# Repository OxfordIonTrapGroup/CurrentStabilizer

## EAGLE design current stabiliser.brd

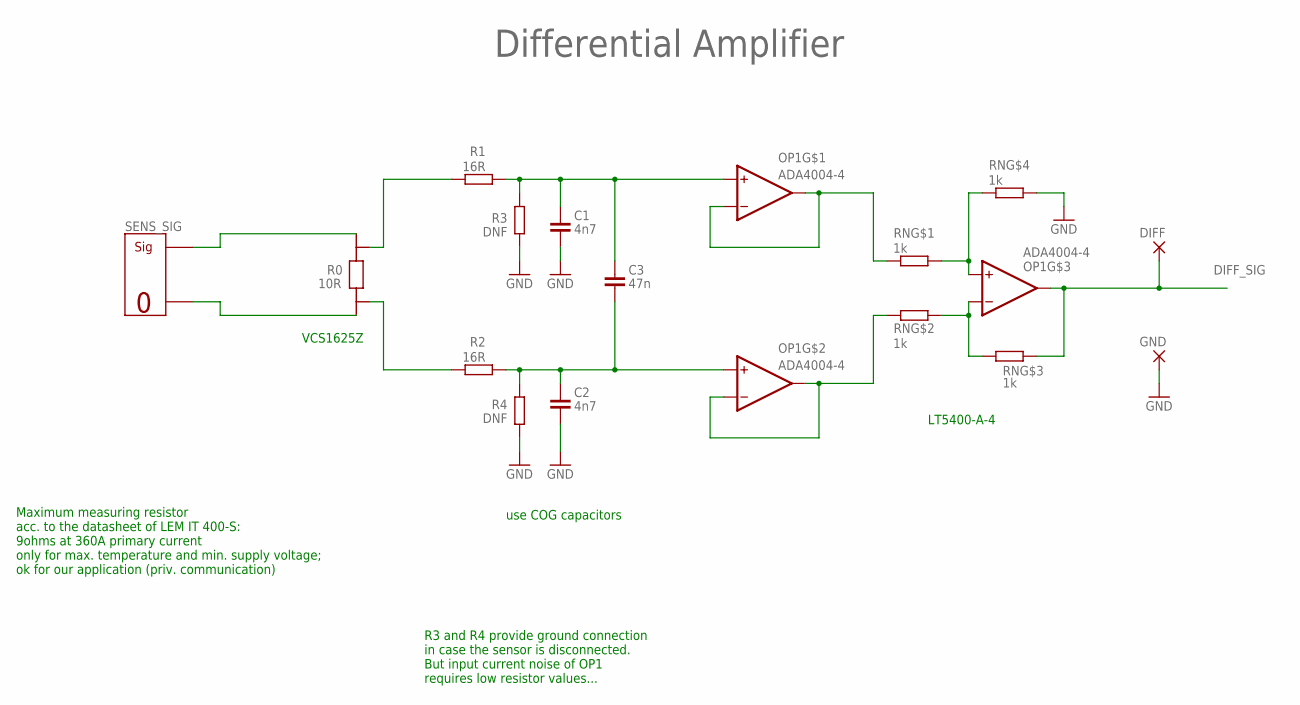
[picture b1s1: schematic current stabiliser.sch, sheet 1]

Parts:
C1, C2: 4n7; 0603
C3: 47n; 0603
DIFF: TESTPOINT
GND: TESTPOINT
OP1: ADA4004-4; SO14
R0: 10R; VCS1625Z
R1, R2: 16R; 0603
R3, R4: DNF; 0603
RN: 1k; MSOP8-EP
SENS_SIG: MOLEX_SIG_2PIN; MOLEX-2PIN

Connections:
DIFF_SIG: DIFF.P$1, OP1.P$8 (OUT), RN.3 (1); also elsewhere on the board
GND: C1.2, C2.2, GND.P$1, R3.1, R4.1, RN.5 (2); also elsewhere on the board
unnamed: R0.P$1 (I1), SENS_SIG.2 (SIG)
unnamed: C2.1, C3.2, OP1.P$5 (+IN), R2.2, R4.2
unnamed: R0.P$4 (E2), R2.1
unnamed: R0.P$3 (E1), R1.1
unnamed: C1.1, C3.1, OP1.P$3 (+IN), R1.2, R3.2
unnamed: OP1.P$1 (OUT), OP1.P$2 (-IN), RN.1
unnamed: OP1.P$6 (-IN), OP1.P$7 (OUT), RN.2 (1)
unnamed: OP1.P$10 (+IN), RN.4 (1), RN.8 (2)
unnamed: OP1.P$9 (-IN), RN.6 (2), RN.7 (2)
SENS_RETURN: R0.P$2 (I2), SENS_SIG.1 (GND)

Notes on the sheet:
Differential Amplifier
use COG capacitors
R3 and R4 provide ground connection in case the sensor is disconnected. But input current noise of OP1 requires low resistor values...
Maximum measuring resistor acc. to the datasheet of LEM IT 400-S: 9ohms at 360A primary current only for max. temperature and min. supply voltage; ok for our application (priv. communication)
VCS1625Z
LT5400-A-4

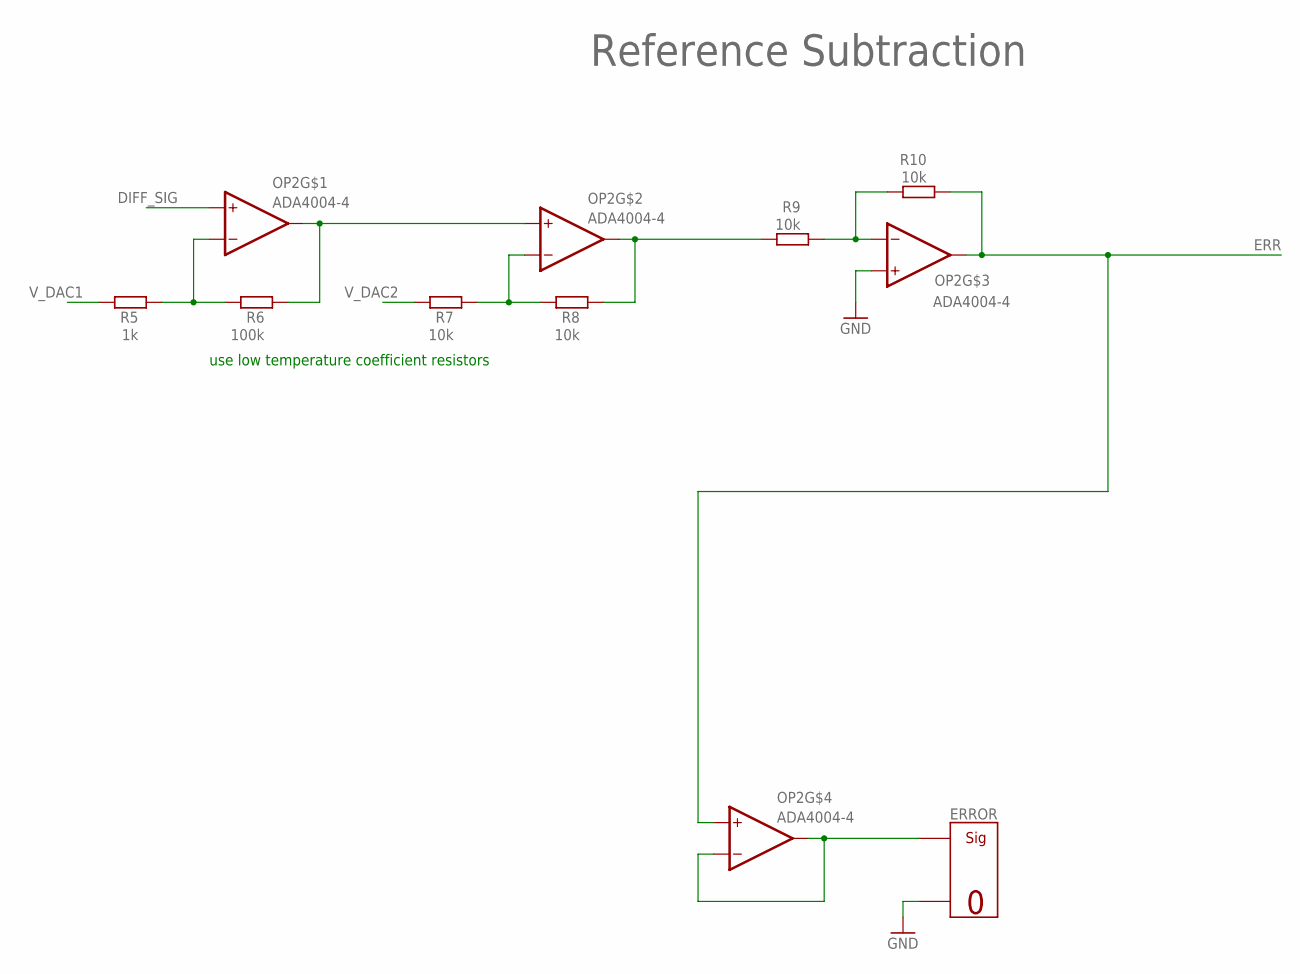
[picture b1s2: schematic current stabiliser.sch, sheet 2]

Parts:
ERROR: MOLEX_SIG_2PIN; MOLEX-2PIN
OP2: ADA4004-4; SO14
R5: 1k; 0603
R6: 100k; 0603
R7, R8, R9, R10: 10k; 0603

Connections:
DIFF_SIG: OP2.P$3 (+IN); also elsewhere on the board
ERR: OP2.P$8 (OUT), OP2.P$12 (+IN), R10.2; also elsewhere on the board
GND: ERROR.1 (GND), OP2.P$10 (+IN); also elsewhere on the board
unnamed: OP2.P$2 (-IN), R5.2, R6.1
unnamed: OP2.P$9 (-IN), R9.2, R10.1
unnamed: OP2.P$1 (OUT), OP2.P$5 (+IN), R6.2
unnamed: OP2.P$6 (-IN), R7.2, R8.1
unnamed: OP2.P$7 (OUT), R8.2, R9.1
unnamed: ERROR.2 (SIG), OP2.P$13 (-IN), OP2.P$14 (OUT)
V_DAC1: R5.1; also elsewhere on the board
V_DAC2: R7.1; also elsewhere on the board

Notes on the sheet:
Reference Subtraction
use low temperature coefficient resistors

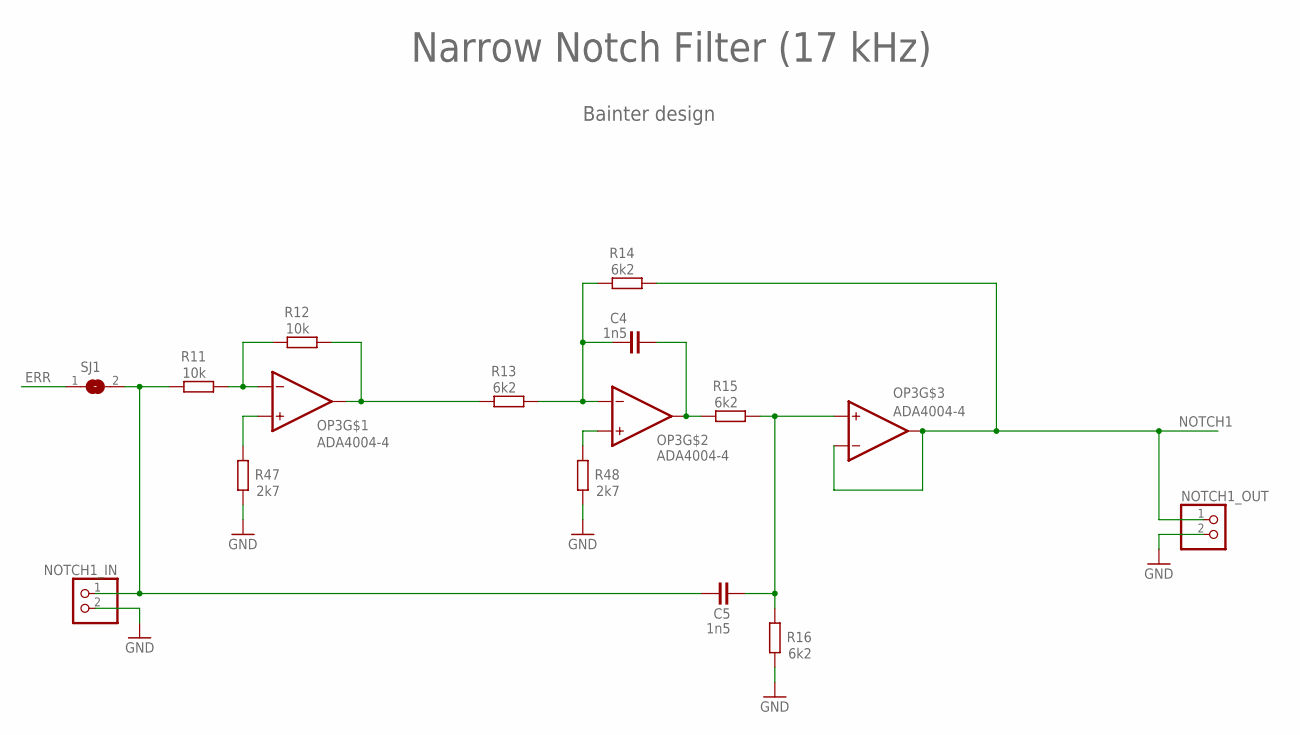
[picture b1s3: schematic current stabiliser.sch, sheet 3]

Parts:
C4, C5: 1n5; 0603
NOTCH1_IN, NOTCH1_OUT: PINHD-1X2; 1X02
OP3: ADA4004-4; SO14
R11, R12: 10k; 0603
R13, R14, R15, R16: 6k2; 0603
R47, R48: 2k7; 0603
SJ1: SJ

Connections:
ERR: SJ1.1; also elsewhere on the board
GND: NOTCH1_IN.2, NOTCH1_OUT.2, R16.2, R47.2, R48.2; also elsewhere on the board
unnamed: OP3.P$2 (-IN), R11.2, R12.1
unnamed: OP3.P$1 (OUT), R12.2, R13.1
unnamed: C4.1, OP3.P$6 (-IN), R13.2, R14.1
unnamed: C4.2, OP3.P$7 (OUT), R15.1
unnamed: C5.2, OP3.P$10 (+IN), R15.2, R16.1
unnamed: C5.1, NOTCH1_IN.1, R11.1, SJ1.2
unnamed: OP3.P$3 (+IN), R47.1
unnamed: OP3.P$5 (+IN), R48.1
NOTCH1: NOTCH1_OUT.1, OP3.P$8 (OUT), OP3.P$9 (-IN), R14.2; also elsewhere on the board

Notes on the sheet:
Narrow Notch Filter (17 kHz)
Bainter design

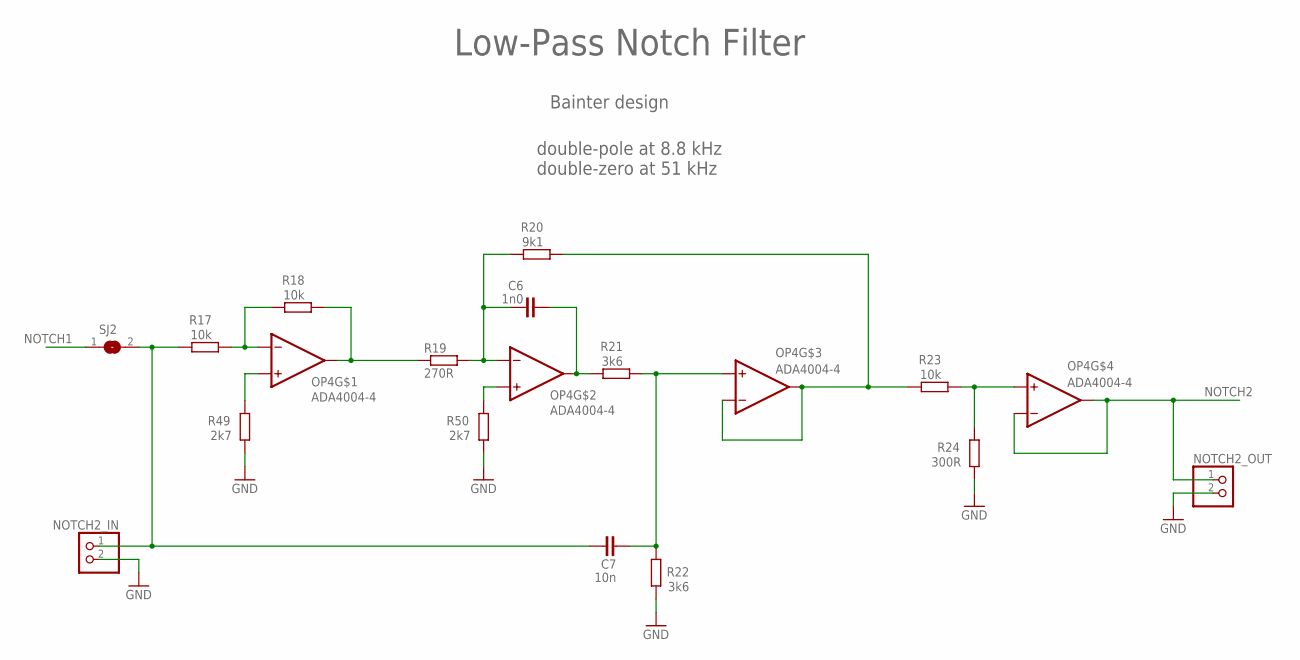
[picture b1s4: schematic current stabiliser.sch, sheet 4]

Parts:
C6: 1n0; 0603
C7: 10n; 0603
NOTCH2_IN, NOTCH2_OUT: PINHD-1X2; 1X02
OP4: ADA4004-4; SO14
R17, R18, R23: 10k; 0603
R19: 270R; 0603
R20: 9k1; 0603
R21, R22: 3k6; 0603
R24: 300R; 0603
R49, R50: 2k7; 0603
SJ2: SJ

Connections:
GND: NOTCH2_IN.2, NOTCH2_OUT.2, R22.1, R24.1, R49.1, R50.1; also elsewhere on the board
unnamed: OP4.P$2 (-IN), R17.2, R18.1
unnamed: OP4.P$1 (OUT), R18.2, R19.1
unnamed: C6.1, OP4.P$6 (-IN), R19.2, R20.1
unnamed: C7.2, OP4.P$10 (+IN), R21.2, R22.2
unnamed: C6.2, OP4.P$7 (OUT), R21.1
unnamed: OP4.P$8 (OUT), OP4.P$9 (-IN), R20.2, R23.1
unnamed: OP4.P$12 (+IN), R23.2, R24.2
unnamed: C7.1, NOTCH2_IN.1, R17.1, SJ2.2
unnamed: OP4.P$3 (+IN), R49.2
unnamed: OP4.P$5 (+IN), R50.2
NOTCH1: SJ2.1; also elsewhere on the board
NOTCH2: NOTCH2_OUT.1, OP4.P$13 (-IN), OP4.P$14 (OUT); also elsewhere on the board

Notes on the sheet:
Low-Pass Notch Filter
double-pole at 8.8 kHz double-zero at 51 kHz
Bainter design

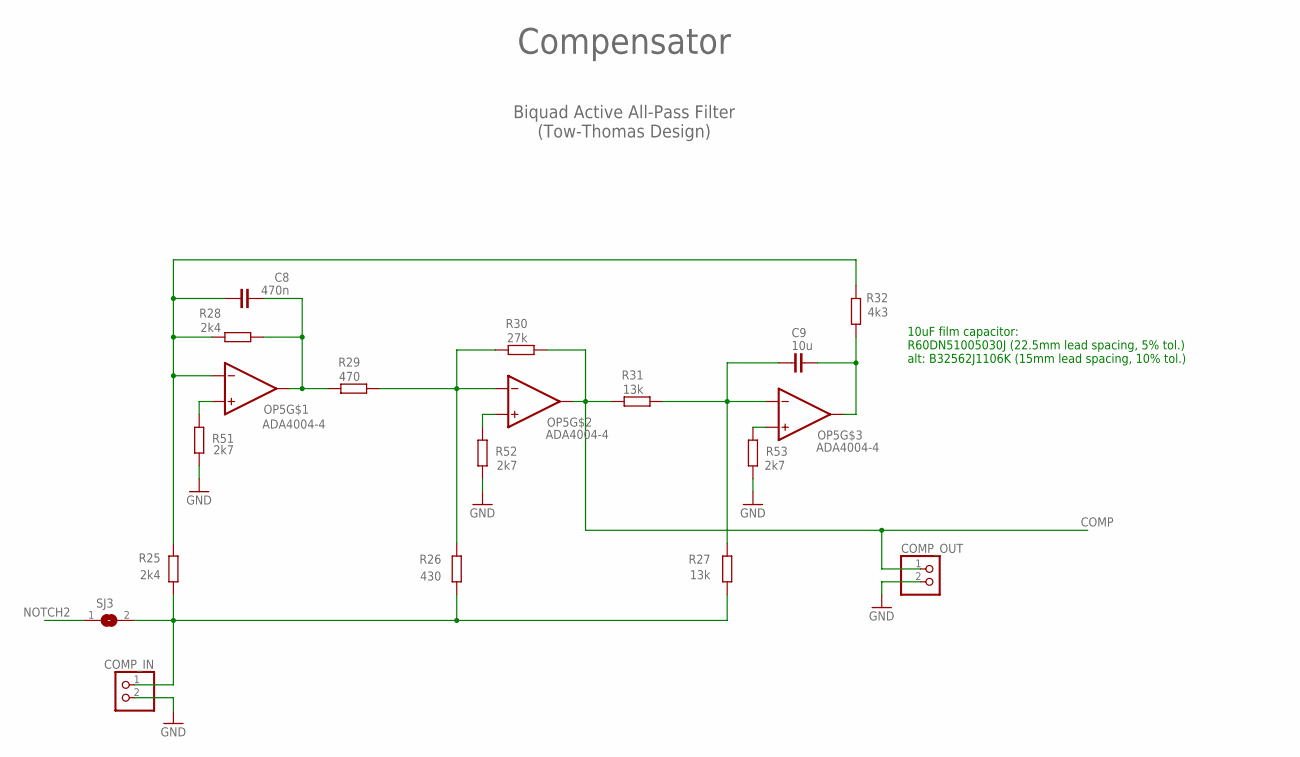
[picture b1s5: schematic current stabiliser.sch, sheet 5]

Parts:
C8: 470n; 0603
C9: 10u; CAP-26.5X8.5
COMP_IN: PINHD-1X2; 1X02
COMP_OUT: PINHD-1X2; 1X02
OP5: ADA4004-4; SO14
R25, R28: 2k4; 0603
R26: 430; 0603
R27, R31: 13k; 0603
R29: 470; 0603
R30: 27k; 0603
R32: 4k3; 0603
R51, R52, R53: 2k7; 0603
SJ3: SJ

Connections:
COMP: COMP_OUT.1, OP5.P$7 (OUT), R30.2, R31.1; also elsewhere on the board
GND: COMP_IN.2, COMP_OUT.2, R51.1, R52.1, R53.1; also elsewhere on the board
unnamed: C8.1, OP5.P$2 (-IN), R25.2, R28.1, R32.2
unnamed: OP5.P$6 (-IN), R26.2, R29.2, R30.1
unnamed: C9.P$1 (1), OP5.P$9 (-IN), R27.2, R31.2
unnamed: C8.2, OP5.P$1 (OUT), R28.2, R29.1
unnamed: C9.P$2 (2), OP5.P$8 (OUT), R32.1
unnamed: COMP_IN.1, R25.1, R26.1, R27.1, SJ3.2
unnamed: OP5.P$3 (+IN), R51.2
unnamed: OP5.P$5 (+IN), R52.2
unnamed: OP5.P$10 (+IN), R53.2
NOTCH2: SJ3.1; also elsewhere on the board

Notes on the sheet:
10uF film capacitor: R60DN51005030J (22.5mm lead spacing, 5% tol.) alt: B32562J1106K (15mm lead spacing, 10% tol.)
Compensator
Biquad Active All-Pass Filter (Tow-Thomas Design)

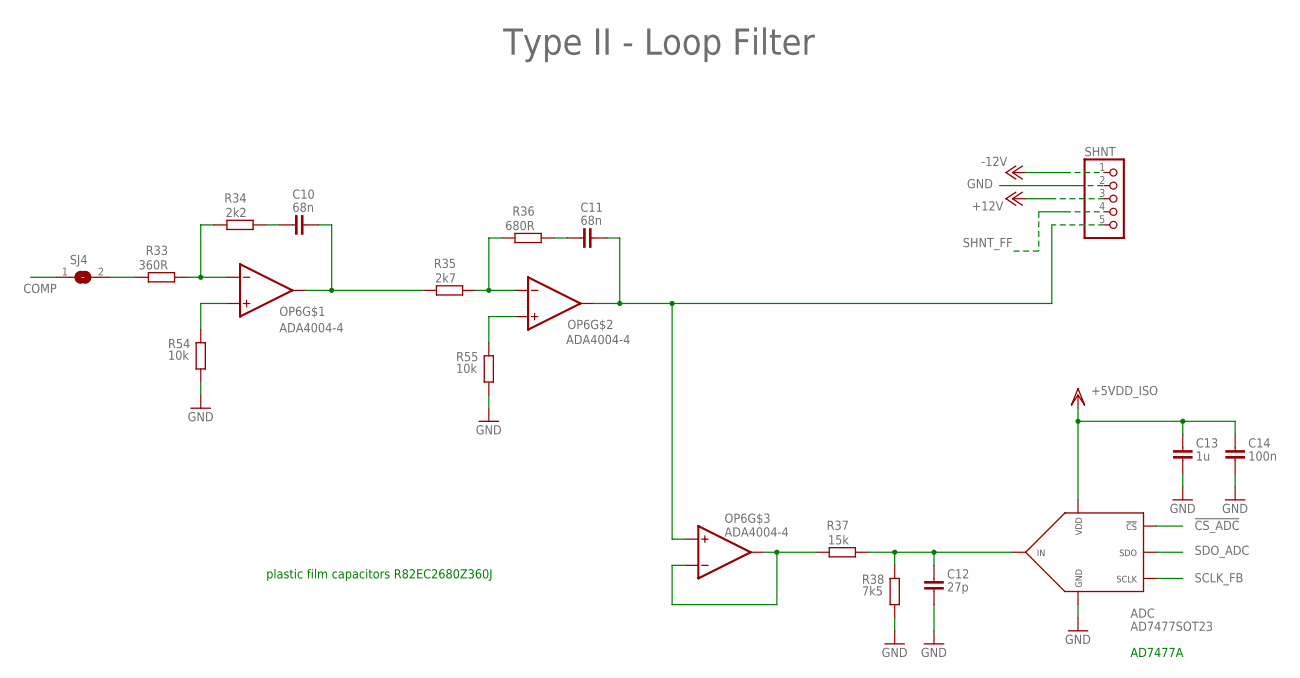
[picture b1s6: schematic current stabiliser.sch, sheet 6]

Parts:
ADC: AD7477SOT23; SOT23-6
C10, C11: 68n; CAP-R82EC-7.2X2.5
C12: 27p; 0603
C13: 1u; 0805
C14: 100n; 0603
OP6: ADA4004-4; SO14
R33: 360R; 0603
R34: 2k2; 0603
R35: 2k7; 0603
R36: 680R; 0603
R37: 15k; 0603
R38: 7k5; 0603
R54, R55: 10k; 0603
SHNT: MOLEX-KK-1X5; MOLEX-KK-5PIN
SJ4: SJ

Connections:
!CS_ADC: ADC.6 (!CS); also elsewhere on the board
+5VDD_ISO: ADC.1 (VDD), C13.1, C14.1; also elsewhere on the board
+12V: SHNT.3; also elsewhere on the board
-12V: SHNT.1; also elsewhere on the board
COMP: SJ4.1; also elsewhere on the board
GND: ADC.2 (GND), C12.2, C13.2, C14.2, R38.1, R54.1, R55.1, SHNT.2; also elsewhere on the board
unnamed: OP6.P$2 (-IN), R33.2, R34.1
unnamed: OP6.P$3 (+IN), R54.2
unnamed: OP6.P$5 (+IN), R55.2
unnamed: OP6.P$6 (-IN), R35.2, R36.1
unnamed: C11.P$1 (1), R36.2
unnamed: C10.P$1 (1), R34.2
unnamed: C10.P$2 (2), OP6.P$1 (OUT), R35.1
unnamed: OP6.P$8 (OUT), OP6.P$9 (-IN), R37.2
unnamed: ADC.3 (IN), C12.1, R37.1, R38.2
unnamed: R33.1, SJ4.2
SCLK_FB: ADC.4 (SCLK); also elsewhere on the board
SDO_ADC: ADC.5 (SDO); also elsewhere on the board
SHNT_FB: C11.P$2 (2), OP6.P$7 (OUT), OP6.P$10 (+IN), SHNT.5
SHNT_FF: SHNT.4; also elsewhere on the board

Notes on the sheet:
plastic film capacitors R82EC2680Z360J
Type II - Loop Filter
AD7477A

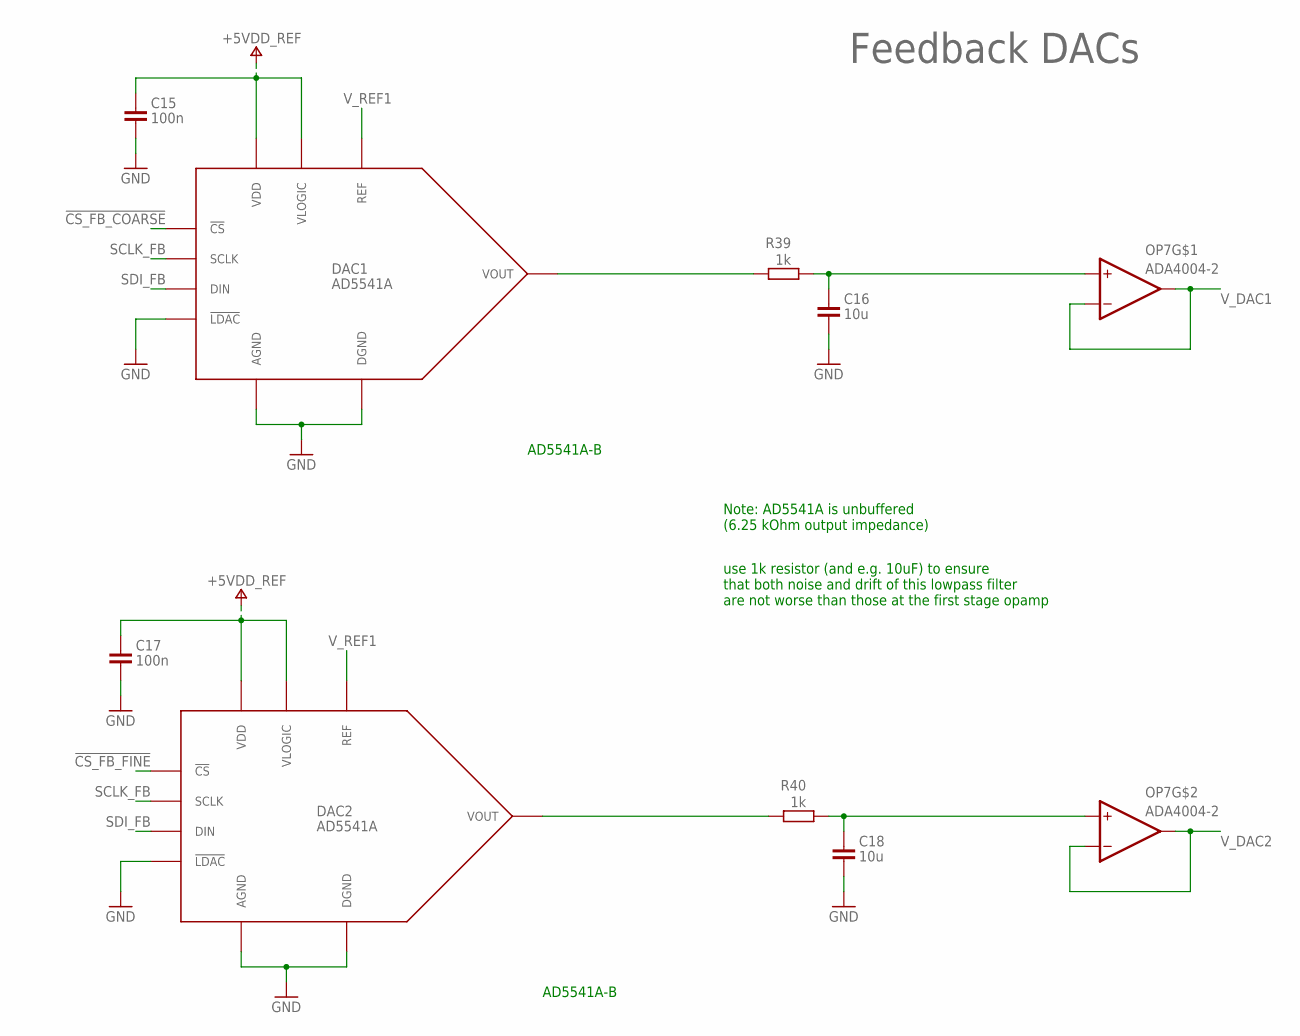
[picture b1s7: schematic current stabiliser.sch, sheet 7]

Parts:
C15, C17: 100n; 0603
C16, C18: 10u; 0805
DAC1, DAC2: AD5541A; MSOP10_LONG
OP7: ADA4004-2; SO8
R39, R40: 1k; 0603

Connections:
!CS_FB_COARSE: DAC1.5 (!CS); also elsewhere on the board
!CS_FB_FINE: DAC2.5 (!CS); also elsewhere on the board
+5VDD_REF: C15.1, C17.1, DAC1.1 (VDD), DAC1.10 (VLOGIC), DAC2.1 (VDD), DAC2.10 (VLOGIC); also elsewhere on the board
GND: C15.2, C16.2, C17.2, C18.2, DAC1.3 (AGND), DAC1.8 (!LDAC), DAC1.9 (DGND), DAC2.3 (AGND), DAC2.8 (!LDAC), DAC2.9 (DGND); also elsewhere on the board
unnamed: DAC1.2 (VOUT), R39.1
unnamed: C16.1, OP7.3 (+IN), R39.2
unnamed: DAC2.2 (VOUT), R40.1
unnamed: C18.1, OP7.5 (+IN), R40.2
SCLK_FB: DAC1.6 (SCLK), DAC2.6 (SCLK); also elsewhere on the board
SDI_FB: DAC1.7 (DIN), DAC2.7 (DIN); also elsewhere on the board
V_DAC1: OP7.1 (OUT), OP7.2 (-IN); also elsewhere on the board
V_DAC2: OP7.6 (-IN), OP7.7 (OUT); also elsewhere on the board
V_REF1: DAC1.4 (REF), DAC2.4 (REF); also elsewhere on the board

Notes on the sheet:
Feedback DACs
use 1k resistor (and e.g. 10uF) to ensure that both noise and drift of this lowpass filter are not worse than those at the first stage opamp
AD5541A-B
Note: AD5541A is unbuffered (6.25 kOhm output impedance)

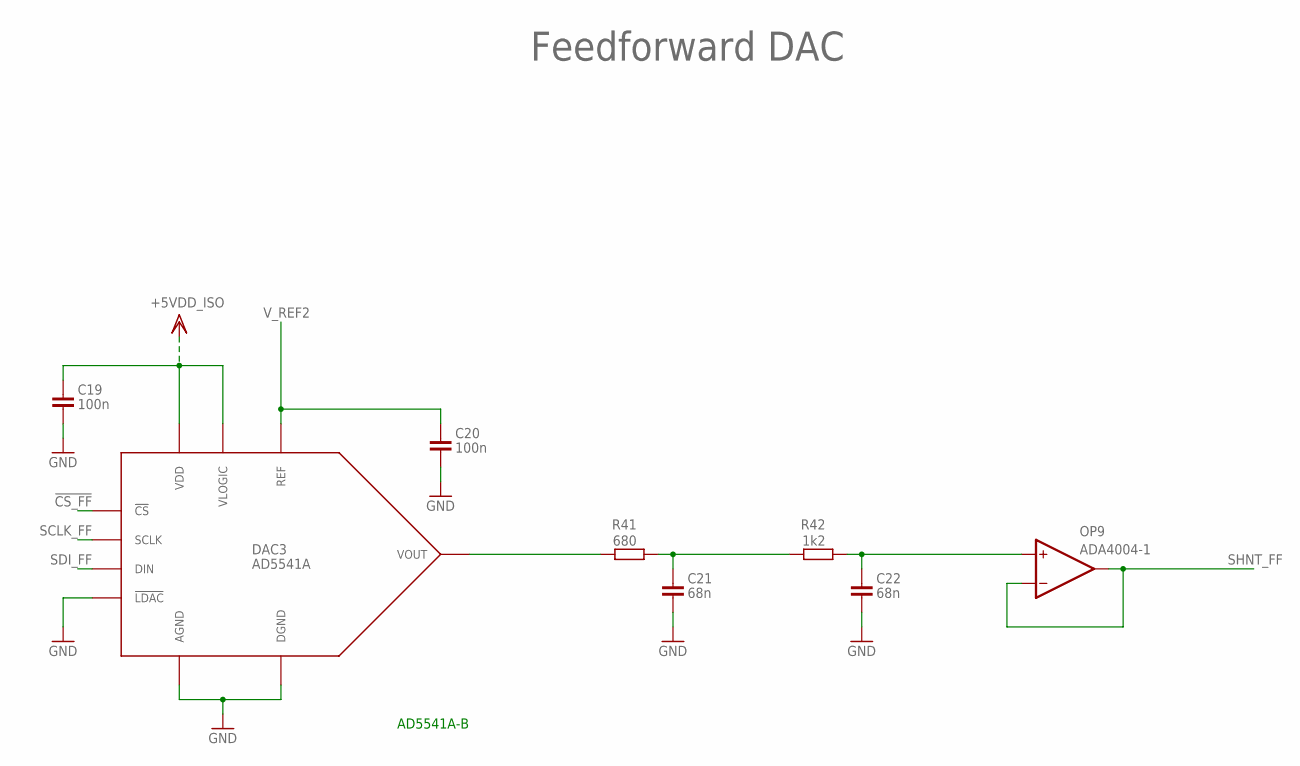
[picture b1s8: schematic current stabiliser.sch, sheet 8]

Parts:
C19, C20: 100n; 0603
C21, C22: 68n; 0603
DAC3: AD5541A; MSOP10_LONG
OP9: ADA4004-1; SOT23-5
R41: 680; 0603
R42: 1k2; 0603

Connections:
!CS_FF: DAC3.5 (!CS); also elsewhere on the board
+5VDD_ISO: C19.1, DAC3.1 (VDD), DAC3.10 (VLOGIC); also elsewhere on the board
GND: C19.2, C20.2, C21.2, C22.2, DAC3.3 (AGND), DAC3.8 (!LDAC), DAC3.9 (DGND); also elsewhere on the board
unnamed: DAC3.2 (VOUT), R41.1
unnamed: C21.1, R41.2, R42.1
unnamed: C22.1, OP9.3 (+IN), R42.2
SCLK_FF: DAC3.6 (SCLK); also elsewhere on the board
SDI_FF: DAC3.7 (DIN); also elsewhere on the board
SHNT_FF: OP9.1 (OUT), OP9.4 (-IN); also elsewhere on the board
V_REF2: C20.1, DAC3.4 (REF); also elsewhere on the board

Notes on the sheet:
Feedforward DAC
AD5541A-B

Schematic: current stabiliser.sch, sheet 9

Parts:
C23, C25, C27: 100n; 0603
C24, C26, C28: 10u; 0805
OP10: ADA4004-4; SO14
R43, R44: 100R; 0603
REF: LTC6655; MSOP8
VREF: TESTPOINT

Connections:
+5VDD_REF: C23.1, REF.1 (!SHDN), REF.2 (VIN); also elsewhere on the board
GND: C23.2, C24.2, C25.2, C26.2, C27.2, C28.2, REF.3 (GND1), REF.4 (GND2), REF.5 (GND3), REF.8 (GND4); also elsewhere on the board
REF: C24.1, OP10.P$3 (+IN), OP10.P$12 (+IN), REF.6 (VOUT_SENSE), REF.7 (VOUT_F), VREF.P$1
V_REF1: OP10.P$6 (-IN), OP10.P$7 (OUT); also elsewhere on the board
V_REF1A: OP10.P$1 (OUT), OP10.P$2 (-IN), R43.2
V_REF1_LP: C25.1, C26.1, OP10.P$5 (+IN), R43.1
V_REF2: OP10.P$8 (OUT), OP10.P$9 (-IN); also elsewhere on the board
V_REF2_LP: C27.1, C28.1, OP10.P$10 (+IN), R44.1
V_REFBUF1: OP10.P$13 (-IN), OP10.P$14 (OUT), R44.2

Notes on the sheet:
output capacitor ESR should be < 0.1 ohms
Voltage Reference
provides 2.048V reference for DACs
ceramic capacitors (low ESR) decouple capacitive load from opamp feedback via 100R (larger than opamp output impedance, smaller than DAC input impedance)
place near short edge of the board or in a corner to reduce sensitivity to mechanical stress

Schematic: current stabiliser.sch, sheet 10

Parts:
ADUM1, ADUM2: ADUM4151B; SOIC_IC-20
C29, C30, C31, C32: 100n; 0603
SPI_CON: SPI_FB; HEADER-2X8-BOX

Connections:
!CS_ADC: ADUM2.15 (!SSS); also elsewhere on the board
!CS_FB_COARSE: ADUM2.14 (VOA); also elsewhere on the board
!CS_FB_FINE: ADUM2.13 (VOB); also elsewhere on the board
!CS_FF: ADUM1.15 (!SSS); also elsewhere on the board
+3V3DIG: ADUM1.1 (VDD1), ADUM2.1 (VDD1), C29.2, C31.2, SPI_CON.15
+5VDD_ISO: ADUM1.20 (VDD2), ADUM2.20 (VDD2), C30.1, C32.1; also elsewhere on the board
DGND: ADUM1.2 (GND1), ADUM1.7 (VIA), ADUM1.8 (VIB), ADUM1.10 (GND1), ADUM2.2 (GND1), ADUM2.10 (GND1), C29.1, C31.1, SPI_CON.1, SPI_CON.3, SPI_CON.5, SPI_CON.7, SPI_CON.9, SPI_CON.11
DIG_FF_CLK: ADUM1.3 (MCLK), SPI_CON.2
DIG_FF_CS: ADUM1.6 (!MSS), SPI_CON.6
DIG_FF_SIG: ADUM1.4 (MO), SPI_CON.4
GND: ADUM1.11 (GND2), ADUM1.12 (VIC), ADUM1.16 (SO), ADUM1.19 (GND2), ADUM2.11 (GND2), ADUM2.12 (VIC), ADUM2.19 (GND2), C30.2, C32.2; also elsewhere on the board
unnamed: ADUM2.4 (MO), SPI_CON.10
unnamed: ADUM2.5 (MI), SPI_CON.12
unnamed: ADUM2.6 (!MSS), SPI_CON.14
unnamed: ADUM2.7 (VIA), SPI_CON.16
unnamed: ADUM2.8 (VIB), SPI_CON.13
unnamed: ADUM2.3 (MCLK), SPI_CON.8
SCLK_FB: ADUM2.18 (SCLK); also elsewhere on the board
SCLK_FF: ADUM1.18 (SCLK); also elsewhere on the board
SDI_FB: ADUM2.17 (SI); also elsewhere on the board
SDI_FF: ADUM1.17 (SI); also elsewhere on the board
SDO_ADC: ADUM2.16 (SO); also elsewhere on the board

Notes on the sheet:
SPI Isolators
watch out for the different orientation of the isolators on the board!
Note: you can also run the ADUM4151B with +5V supply voltage on either side, which supports slightly higher clock rates (up to 17MHz)

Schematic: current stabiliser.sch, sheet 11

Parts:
+5V, +12V: TPS7A4700; QFN20_5
-12V: TPS7A33; QFN20_5
C33, C36, C40, C63, C65: 10u; 0805
C34, C37, C41: 1u; 0805
C35, C39, C42: 47u; 1206
C38: 10n; 0805
C64, C66: 100n; 0603
D1, D2, D3: DIODE_SCHOTTKY; SOD523
R45: 1.5M; 0603
R46: 162k; 0603
R56, R57: 10R; 0603

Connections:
+5V: +5V.P$1 (OUT), +5V.P$3 (FB), +5V.P$20 (OUT1), C42.1, D2.K, R56.1, R57.1
+5VDD_ISO: C65.1, C66.1, R57.2; also elsewhere on the board
+5VDD_REF: C63.1, C64.1, R56.2; also elsewhere on the board
+12V: +12V.P$1 (OUT), +12V.P$3 (FB), +12V.P$20 (OUT1), C35.1, D1.K; also elsewhere on the board
+15V: +5V.P$13 (EN), +5V.P$15 (IN), +5V.P$16 (IN1), +12V.P$13 (EN), +12V.P$15 (IN), +12V.P$16 (IN1), C33.1, C40.1; also elsewhere on the board
-12V: -12V.P$1 (OUT), -12V.P$20 (OUT1), C38.1, C39.1, D3.A, R45.2; also elsewhere on the board
-15V: -12V.P$13 (EN), -12V.P$15 (IN), -12V.P$16 (IN1), C36.1; also elsewhere on the board
GND: +5V.EP, +5V.P$2 (NC), +5V.P$6 (3P2V), +5V.P$7 (GND), +5V.P$10 (0P4V), +5V.P$17 (NC1), +5V.P$18 (NC2), +5V.P$19 (NC3), +12V.EP, +12V.P$2 (NC), +12V.P$4 (6P4V1), +12V.P$6 (3P2V), +12V.P$7 (GND), +12V.P$9 (0P8V), +12V.P$11 (0P2V), +12V.P$17 (NC1), +12V.P$18 (NC2), +12V.P$19 (NC3), -12V.EP, -12V.P$2 (NC), -12V.P$4 (NC1), -12V.P$5 (NC2), -12V.P$6 (NC3), -12V.P$7 (GND), -12V.P$8 (NC4), -12V.P$9 (NC5), -12V.P$10 (NC6), -12V.P$11 (NC7), -12V.P$12 (NC8), -12V.P$17 (NC9), -12V.P$18 (NC10), -12V.P$19 (NC11), C33.2, C34.2, C35.2, C36.2, C37.2, C39.2, C40.2, C41.2, C42.2, C63.2, C64.2, C65.2, C66.2, D1.A, D2.A, D3.K, R46.1; also elsewhere on the board
unnamed: +5V.P$14 (NR), C41.1
unnamed: +12V.P$14 (NR), C34.1
unnamed: -12V.P$3 (FB), C38.2, R45.1, R46.2
unnamed: -12V.P$14 (NR), C37.1

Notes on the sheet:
Voltage Regulators
+12V, -12V for OpAmp Power Supply +5V for DACs/ADC, SPI Isolators and Reference LTC6655 Power Supply
low ESR ceramic (X7R, or X5R) input/output capacitors
if output ringing occurs: put 10uF tantalum capacitor (high ESR) in parallel to the 10u ceramic input capacitor

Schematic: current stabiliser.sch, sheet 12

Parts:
C43, C44: 10u; 0805
C45, C46, C47, C48, C49, C50, C51, C52, C53, C54, C55, C56, C57, C58, C59, C60, C61, C62: 100n; 0603
H1, H2, H3, H4: MOUNT-PAD-ROUND3.0; 3,0-PAD
OP1, OP2, OP3, OP4, OP5, OP6, OP10: ADA4004-4; SO14
OP7: ADA4004-2; SO8
OP9: ADA4004-1; SOT23-5
PWR_IN: MOLEX_POWER_3PINKK; MOLEX-3PIN
RN: 1k; MSOP8-EP

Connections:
+12V: C45.1, C47.1, C49.1, C51.1, C53.1, C55.1, C57.1, C59.1, C61.1, OP1.P$4 (V+), OP2.P$4 (V+), OP3.P$4 (V+), OP4.P$4 (V+), OP5.P$4 (V+), OP6.P$4 (V+), OP7.8 (V+), OP9.5 (V+), OP10.P$4 (V+); also elsewhere on the board
+15V: C43.1, PWR_IN.3 (+); also elsewhere on the board
-12V: C46.1, C48.1, C50.1, C52.1, C54.1, C56.1, C58.1, C60.1, C62.1, OP1.P$11 (V-), OP2.P$11 (V-), OP3.P$11 (V-), OP4.P$11 (V-), OP5.P$11 (V-), OP6.P$11 (V-), OP7.4 (V-), OP9.2 (V-), OP10.P$11 (V-); also elsewhere on the board
-15V: C44.1, PWR_IN.1 (-); also elsewhere on the board
GND: C43.2, C44.2, C45.2, C46.2, C47.2, C48.2, C49.2, C50.2, C51.2, C52.2, C53.2, C54.2, C55.2, C56.2, C57.2, C58.2, C59.2, C60.2, C61.2, C62.2, PWR_IN.2 (0), RN.EP; also elsewhere on the board

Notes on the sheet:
Decoupling capacitors
ADA4004-2 after feedback DACs
ADA4004-1 after feedforward DACs
resistor network exposed pad
ADA4004-4 reference buffer

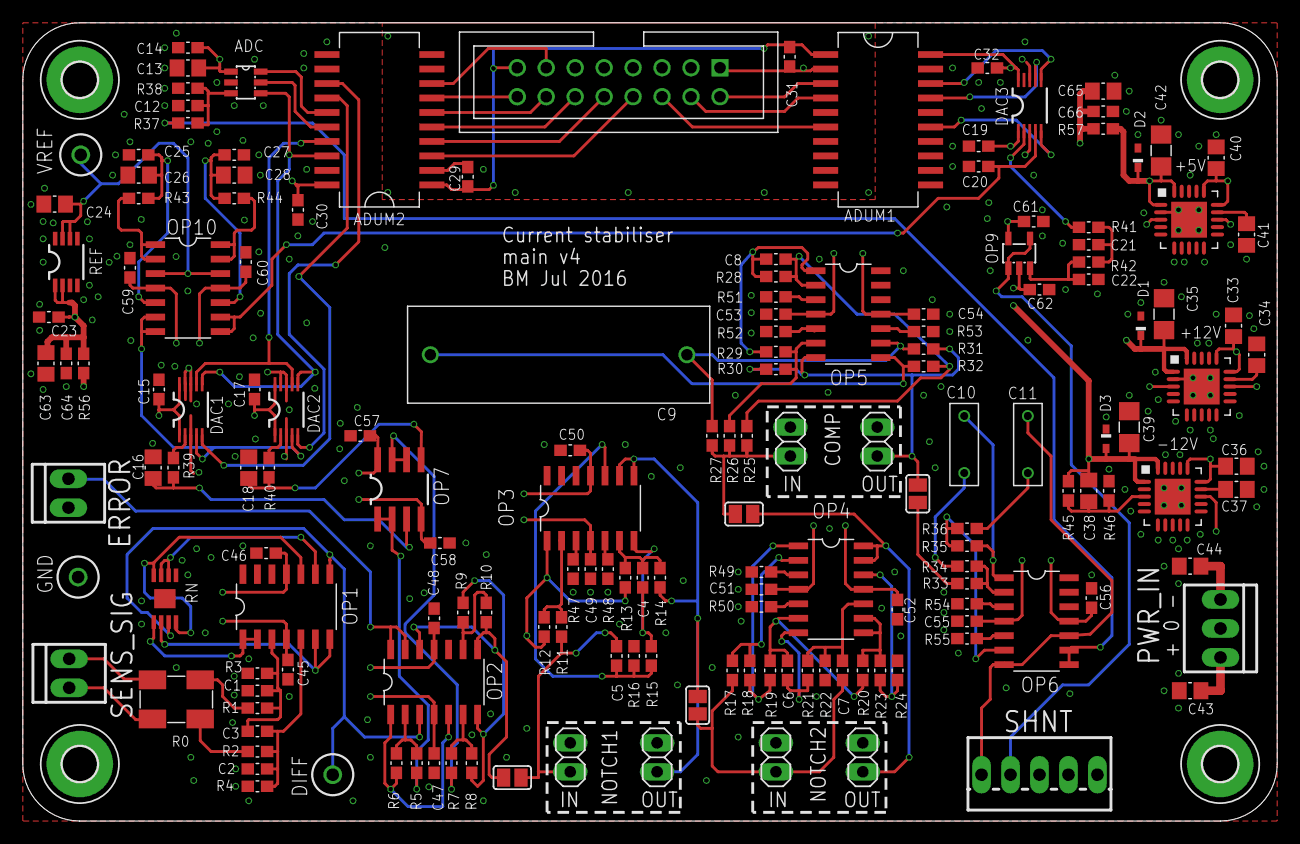
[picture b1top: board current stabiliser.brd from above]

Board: 4 copper layers, 110.0 x 70.0 mm, 169 parts (0 on the bottom side), 108 nets.

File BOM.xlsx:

Part | Value | Device | Package | Description
R26 | 430 | RES0603 | 603
R29 | 470 | RES0603 | 603
R41 | 680 | RES0603 | 603
R56 | 0R | RES0603 | 603
R45 | 1.5M | RES0603 | 603
R6 | 100k | RES0603 | 603
C14 | 100n | CAP0603 | 603 | capacitor
C15 | 100n | CAP0603 | 603 | capacitor
C17 | 100n | CAP0603 | 603 | capacitor
C19 | 100n | CAP0603 | 603 | capacitor
C20 | 100n | CAP0603 | 603 | capacitor
C23 | 100n | CAP0603 | 603 | capacitor
C25 | 100n | CAP0603 | 603 | capacitor
C27 | 100n | CAP0603 | 603 | capacitor
C29 | 100n | CAP0603 | 603 | capacitor
C30 | 100n | CAP0603 | 603 | capacitor
C31 | 100n | CAP0603 | 603 | capacitor
C32 | 100n | CAP0603 | 603 | capacitor
C45 | 100n | CAP0603 | 603 | capacitor
C46 | 100n | CAP0603 | 603 | capacitor
C47 | 100n | CAP0603 | 603 | capacitor
C48 | 100n | CAP0603 | 603 | capacitor
C49 | 100n | CAP0603 | 603 | capacitor
C50 | 100n | CAP0603 | 603 | capacitor
C51 | 100n | CAP0603 | 603 | capacitor
C52 | 100n | CAP0603 | 603 | capacitor
C53 | 100n | CAP0603 | 603 | capacitor
C54 | 100n | CAP0603 | 603 | capacitor
C55 | 100n | CAP0603 | 603 | capacitor
C56 | 100n | CAP0603 | 603 | capacitor
C57 | 100n | CAP0603 | 603 | capacitor
C58 | 100n | CAP0603 | 603 | capacitor
C59 | 100n | CAP0603 | 603 | capacitor
C60 | 100n | CAP0603 | 603 | capacitor
C61 | 100n | CAP0603 | 603 | capacitor
C62 | 100n | CAP0603 | 603 | capacitor
C64 | 100n | CAP0603 | 603 | capacitor
C66 | 100n | CAP0603 | 603 | capacitor
R43 | 100R | RES0603 | 603
R44 | 100R | RES0603 | 603
R7 | 10k | RES0603 | 603
R8 | 10k | RES0603 | 603
R9 | 10k | RES0603 | 603
R10 | 10k | RES0603 | 603
R11 | 10k | RES0603 | 603
R12 | 10k | RES0603 | 603
R17 | 10k | RES0603 | 603
R18 | 10k | RES0603 | 603
R23 | 10k | RES0603 | 603
R54 | 10k | RES0603 | 603
R55 | 10k | RES0603 | 603
C7 | 10n | CAP0603 | 603 | capacitor
C38 | 10n | CAP0805 | 805 | capacitor
R0 | 10R | VCS1625Z | VCS1625Z | 4-terminal Kelvin-connection resistor.
R57 | 10R | RES0603 | 603
C9 | 10u | CAP26.5X8.5 | CAP-26.5X8.5 | capacitor
C16 | 10u | CAP0805 | 805 | capacitor
C18 | 10u | CAP0805 | 805 | capacitor
C24 | 10u | CAP0805 | 805 | capacitor
C26 | 10u | CAP0805 | 805 | capacitor
C28 | 10u | CAP0805 | 805 | capacitor
C33 | 10u | CAP0805 | 805 | capacitor
C36 | 10u | CAP0805 | 805 | capacitor
C40 | 10u | CAP0805 | 805 | capacitor
C43 | 10u | CAP0805 | 805 | capacitor
C44 | 10u | CAP0805 | 805 | capacitor
C63 | 10u | CAP0805 | 805 | capacitor
C65 | 10u | CAP0805 | 805 | capacitor
R27 | 13k | RES0603 | 603
R31 | 13k | RES0603 | 603
R37 | 15k | RES0603 | 603
R46 | 162k | RES0603 | 603
R1 | 16R | RES0603 | 603
R2 | 16R | RES0603 | 603
R5 | 1k | RES0603 | 603
R24 | 1k | RES0603 | 603
R39 | 1k | RES0603 | 603
R40 | 1k | RES0603 | 603
RN | 1k | LT5400-EP | MSOP8-EP | Array of 1k resistors (Digikey part number LT5400AHMS8E-4#PBF-ND).
R42 | 1k2 | RES0603 | 603
C6 | 1n0 | CAP0603 | 603 | capacitor
C4 | 1n5 | CAP0603 | 603 | capacitor
C5 | 1n5 | CAP0603 | 603 | capacitor
C13 | 1u | CAP0805 | 805 | capacitor
C34 | 1u | CAP0805 | 805 | capacitor
C37 | 1u | CAP0805 | 805 | capacitor
C41 | 1u | CAP0805 | 805 | capacitor
R30 | 27k | RES0603 | 603
C12 | 27p | CAP0603 | 603 | capacitor
R21 | 2k | RES0603 | 603
R22 | 2k | RES0603 | 603
R34 | 2k2 | RES0603 | 603
R25 | 2k4 | RES0603 | 603
R28 | 2k4 | RES0603 | 603
R35 | 2k7 | RES0603 | 603
R47 | 2k7 | RES0603 | 603
R48 | 2k7 | RES0603 | 603
R49 | 2k7 | RES0603 | 603
R50 | 2k7 | RES0603 | 603
R51 | 2k7 | RES0603 | 603
R52 | 2k7 | RES0603 | 603
R53 | 2k7 | RES0603 | 603
R33 | 360R | RES0603 | 603
R58 | 390R | RES0603 | 603
R59 | 390R | RES0603 | 603
C8 | 470n | CAP0603 | 603 | capacitor
R19 | 470R | RES0603 | 603
C3 | 47n | CAP0603 | 603 | capacitor
C35 | 47u | CAP1206 | 1206 | capacitor
C39 | 47u | CAP1206 | 1206 | capacitor
C42 | 47u | CAP1206 | 1206 | capacitor
R32 | 4k3 | RES0603 | 603
R20 | 4k7 | RES0603 | 603
C1 | 4n7 | CAP0603 | 603 | capacitor
C2 | 4n7 | CAP0603 | 603 | capacitor
R36 | 680R | RES0603 | 603
C10 | 68n | CAPR82EC-7.2X2.5 | CAP-R82EC-7.2X2.5 | capacitor
C11 | 68n | CAPR82EC-7.2X2.5 | CAP-R82EC-7.2X2.5 | capacitor
C21 | 68n | CAP0603 | 603 | capacitor
C22 | 68n | CAP0603 | 603 | capacitor
R13 | 6k2 | RES0603 | 603
R14 | 6k2 | RES0603 | 603
R15 | 6k2 | RES0603 | 603
R16 | 6k2 | RES0603 | 603
R38 | 7k5 | RES0603 | 603
DAC1 | AD5541A | AD5541A | MSOP10_LONG | 16-bit DAC (Farnell part number 1843653).
DAC2 | AD5541A | AD5541A | MSOP10_LONG | 16-bit DAC (Farnell part number 1843653).
DAC3 | AD5541A | AD5541A | MSOP10_LONG | 16-bit DAC (Farnell part number 1843653).
ADC | AD7477SOT23 | AD7477SOT23 | SOT23-6 | Analog Devices AD7477 10-bit 1MSPS ADC.
OP9 | ADA4004-1 | OPAMPSOT23-5 | SOT23-5 | Suitable for most OpAmps.
OP7 | ADA4004-2 | OPAMP_DUAL | SO8 | Dual op amp
OP1 | ADA4004-4 | OPAMP_QUADSO14 | SO14 | Quad OpAmp
OP2 | ADA4004-4 | OPAMP_QUADSO14 | SO14 | Quad OpAmp
OP3 | ADA4004-4 | OPAMP_QUADSO14 | SO14 | Quad OpAmp
OP4 | ADA4004-4 | OPAMP_QUADSO14 | SO14 | Quad OpAmp
OP5 | ADA4004-4 | OPAMP_QUADSO14 | SO14 | Quad OpAmp
OP6 | ADA4004-4 | OPAMP_QUADSO14 | SO14 | Quad OpAmp
OP10 | ADA4004-4 | OPAMP_QUADSO14 | SO14 | Quad OpAmp
ADUM1 | ADUM4151B | ADUM4151SOIC_IC-20 | SOIC_IC-20 | Analog Devices ADUM4151 SPI Digital Isolator.
ADUM2 | ADUM4151B | ADUM4151SOIC_IC-20 | SOIC_IC-20 | Analog Devices ADUM4151 SPI Digital Isolator.
D1 | DIODE_SCHOTTKY | DIODE_SCHOTTKY | SOD523 | Schottky diodes.
D2 | DIODE_SCHOTTKY | DIODE_SCHOTTKY | SOD523 | Schottky diodes.
D3 | DIODE_SCHOTTKY | DIODE_SCHOTTKY | SOD523 | Schottky diodes.
R3 | DNF | RES0603 | 603
R4 | DNF | RES0603 | 603
REF | LTC6655LS8 | LTC6655LS8 | LS8
PWR_IN | MOLEX_POWER_3PINKK | MOLEX_POWER_3PINKK | MOLEX-3PIN
ERROR | MOLEX_SIG_2PIN | MOLEX_SIG_2PIN | MOLEX-2PIN | 2 pin Molex KK connector for 1 signal puls GND.
SENS_SIG | MOLEX_SIG_2PIN | MOLEX_SIG_2PIN | MOLEX-2PIN | 2 pin Molex KK connector for 1 signal puls GND.
SHNT | MOLEX-KK-1X5 | MOLEX-KK-1X5 | MOLEX-KK-5PIN | Molex KK 6373 Series 2.54mm pitch
H1 | MOUNT-PAD-ROUND3.0 | MOUNT-PAD-ROUND3.0 | 3,0-PAD | MOUNTING PAD, round
H2 | MOUNT-PAD-ROUND3.0 | MOUNT-PAD-ROUND3.0 | 3,0-PAD | MOUNTING PAD, round
H3 | MOUNT-PAD-ROUND3.0 | MOUNT-PAD-ROUND3.0 | 3,0-PAD | MOUNTING PAD, round
H4 | MOUNT-PAD-ROUND3.0 | MOUNT-PAD-ROUND3.0 | 3,0-PAD | MOUNTING PAD, round
SPI_CON | SPI_FB | HEADER-2X8 | HEADER-2X8-BOX
DIFF | TESTPOINT | TESTPOINT | TESTPOINT | Testpoint terminal
GND | TESTPOINT | TESTPOINT | TESTPOINT | Testpoint terminal
VREF | TESTPOINT | TESTPOINT | TESTPOINT | Testpoint terminal
-12V | TPS7A33 | TPS7A33 | QFN20_5
+5V | TPS7A4700 | TPS7A470X | QFN20_5
+12V | TPS7A4700 | TPS7A470X | QFN20_5
COMP_IN |  | PINHD-1X2 | 1X02 | PIN HEADER
COMP_OUT |  | PINHD-1X2 | 1X02 | PIN HEADER
NOTCH1_IN |  | PINHD-1X2 | 1X02 | PIN HEADER
NOTCH1_OUT |  | PINHD-1X2 | 1X02 | PIN HEADER
NOTCH2_IN |  | PINHD-1X2 | 1X02 | PIN HEADER
NOTCH2_OUT |  | PINHD-1X2 | 1X02 | PIN HEADER
SJ1 |  | SJ | SJ | SMD solder JUMPER
SJ2 |  | SJ | SJ | SMD solder JUMPER
SJ3 |  | SJ | SJ | SMD solder JUMPER
SJ4 |  | SJ | SJ | SMD solder JUMPER

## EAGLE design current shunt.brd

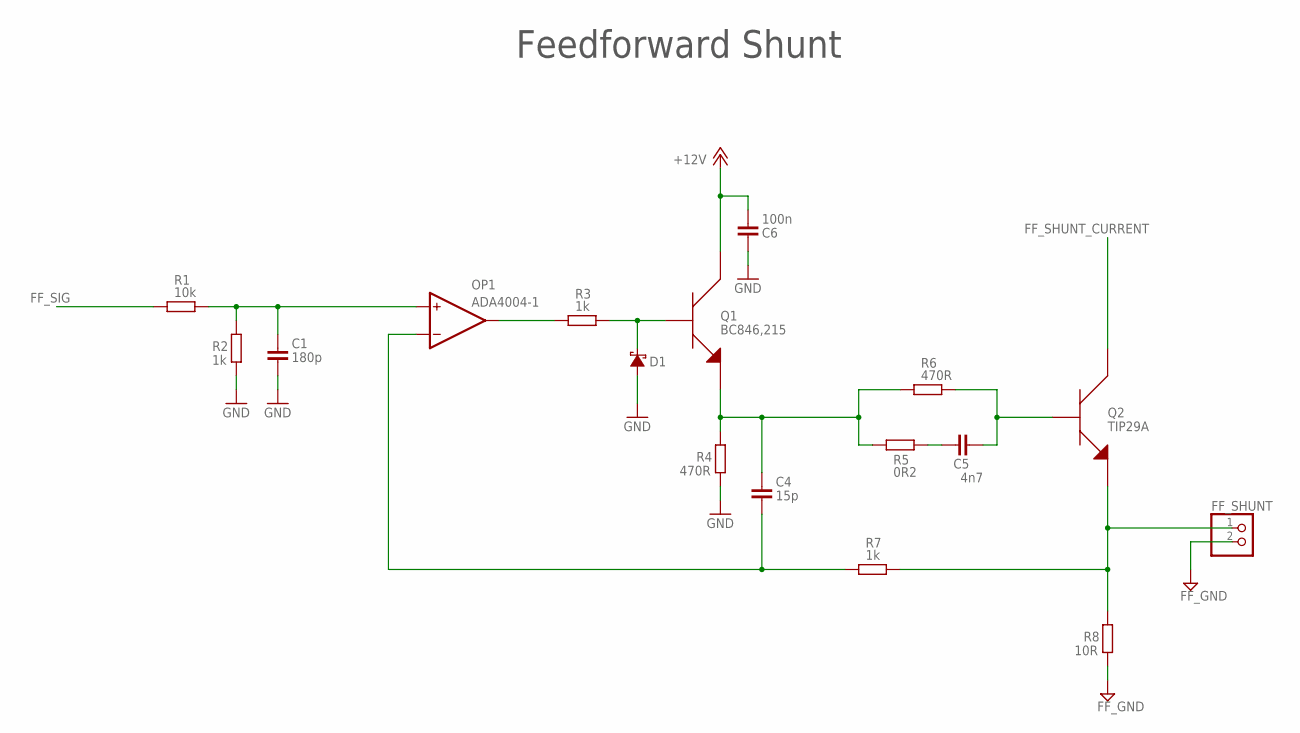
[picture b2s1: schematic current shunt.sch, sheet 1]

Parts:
C1: 180p; 0603
C4: 15p; 0603
C5: 4n7; 0603
C6: 100n; 0603
D1: DIODE_SCHOTTKY; SOD123F
FF_SHUNT: PINHD-1X2; 1X02
OP1: ADA4004-1; SOT23-5
Q1: BC846,215; SOT23
Q2: TIP29A; TO-220_DETATCHED
R1: 10k; 0603
R2, R3, R7: 1k; 0603
R4, R6: 470R; 0603
R5: 0R2; 0603
R8: 10R; 0603

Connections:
+12V: C6.1, Q1.3 (COLLECTOR); also elsewhere on the board
FB_SHUNT: FF_SHUNT.1, Q2.EMITTER, R7.2, R8.2
FF_GND: FF_SHUNT.2, R8.1; also elsewhere on the board
FF_SHUNT_CURRENT: Q2.COLLECTOR; also elsewhere on the board
FF_SIG: R1.1; also elsewhere on the board
GND: C1.2, C6.2, D1.P$2 (A), R2.1, R4.1; also elsewhere on the board
unnamed: C4.2, OP1.4 (-IN), R7.1
unnamed: C1.1, OP1.3 (+IN), R1.2, R2.2
unnamed: C5.1, R5.2
unnamed: OP1.1 (OUT), R3.1
unnamed: D1.P$1 (K), Q1.1 (BASE), R3.2
unnamed: C4.1, Q1.2 (EMITTER), R4.2, R5.1, R6.1
unnamed: C5.2, Q2.BASE, R6.2

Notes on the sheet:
Feedforward Shunt
